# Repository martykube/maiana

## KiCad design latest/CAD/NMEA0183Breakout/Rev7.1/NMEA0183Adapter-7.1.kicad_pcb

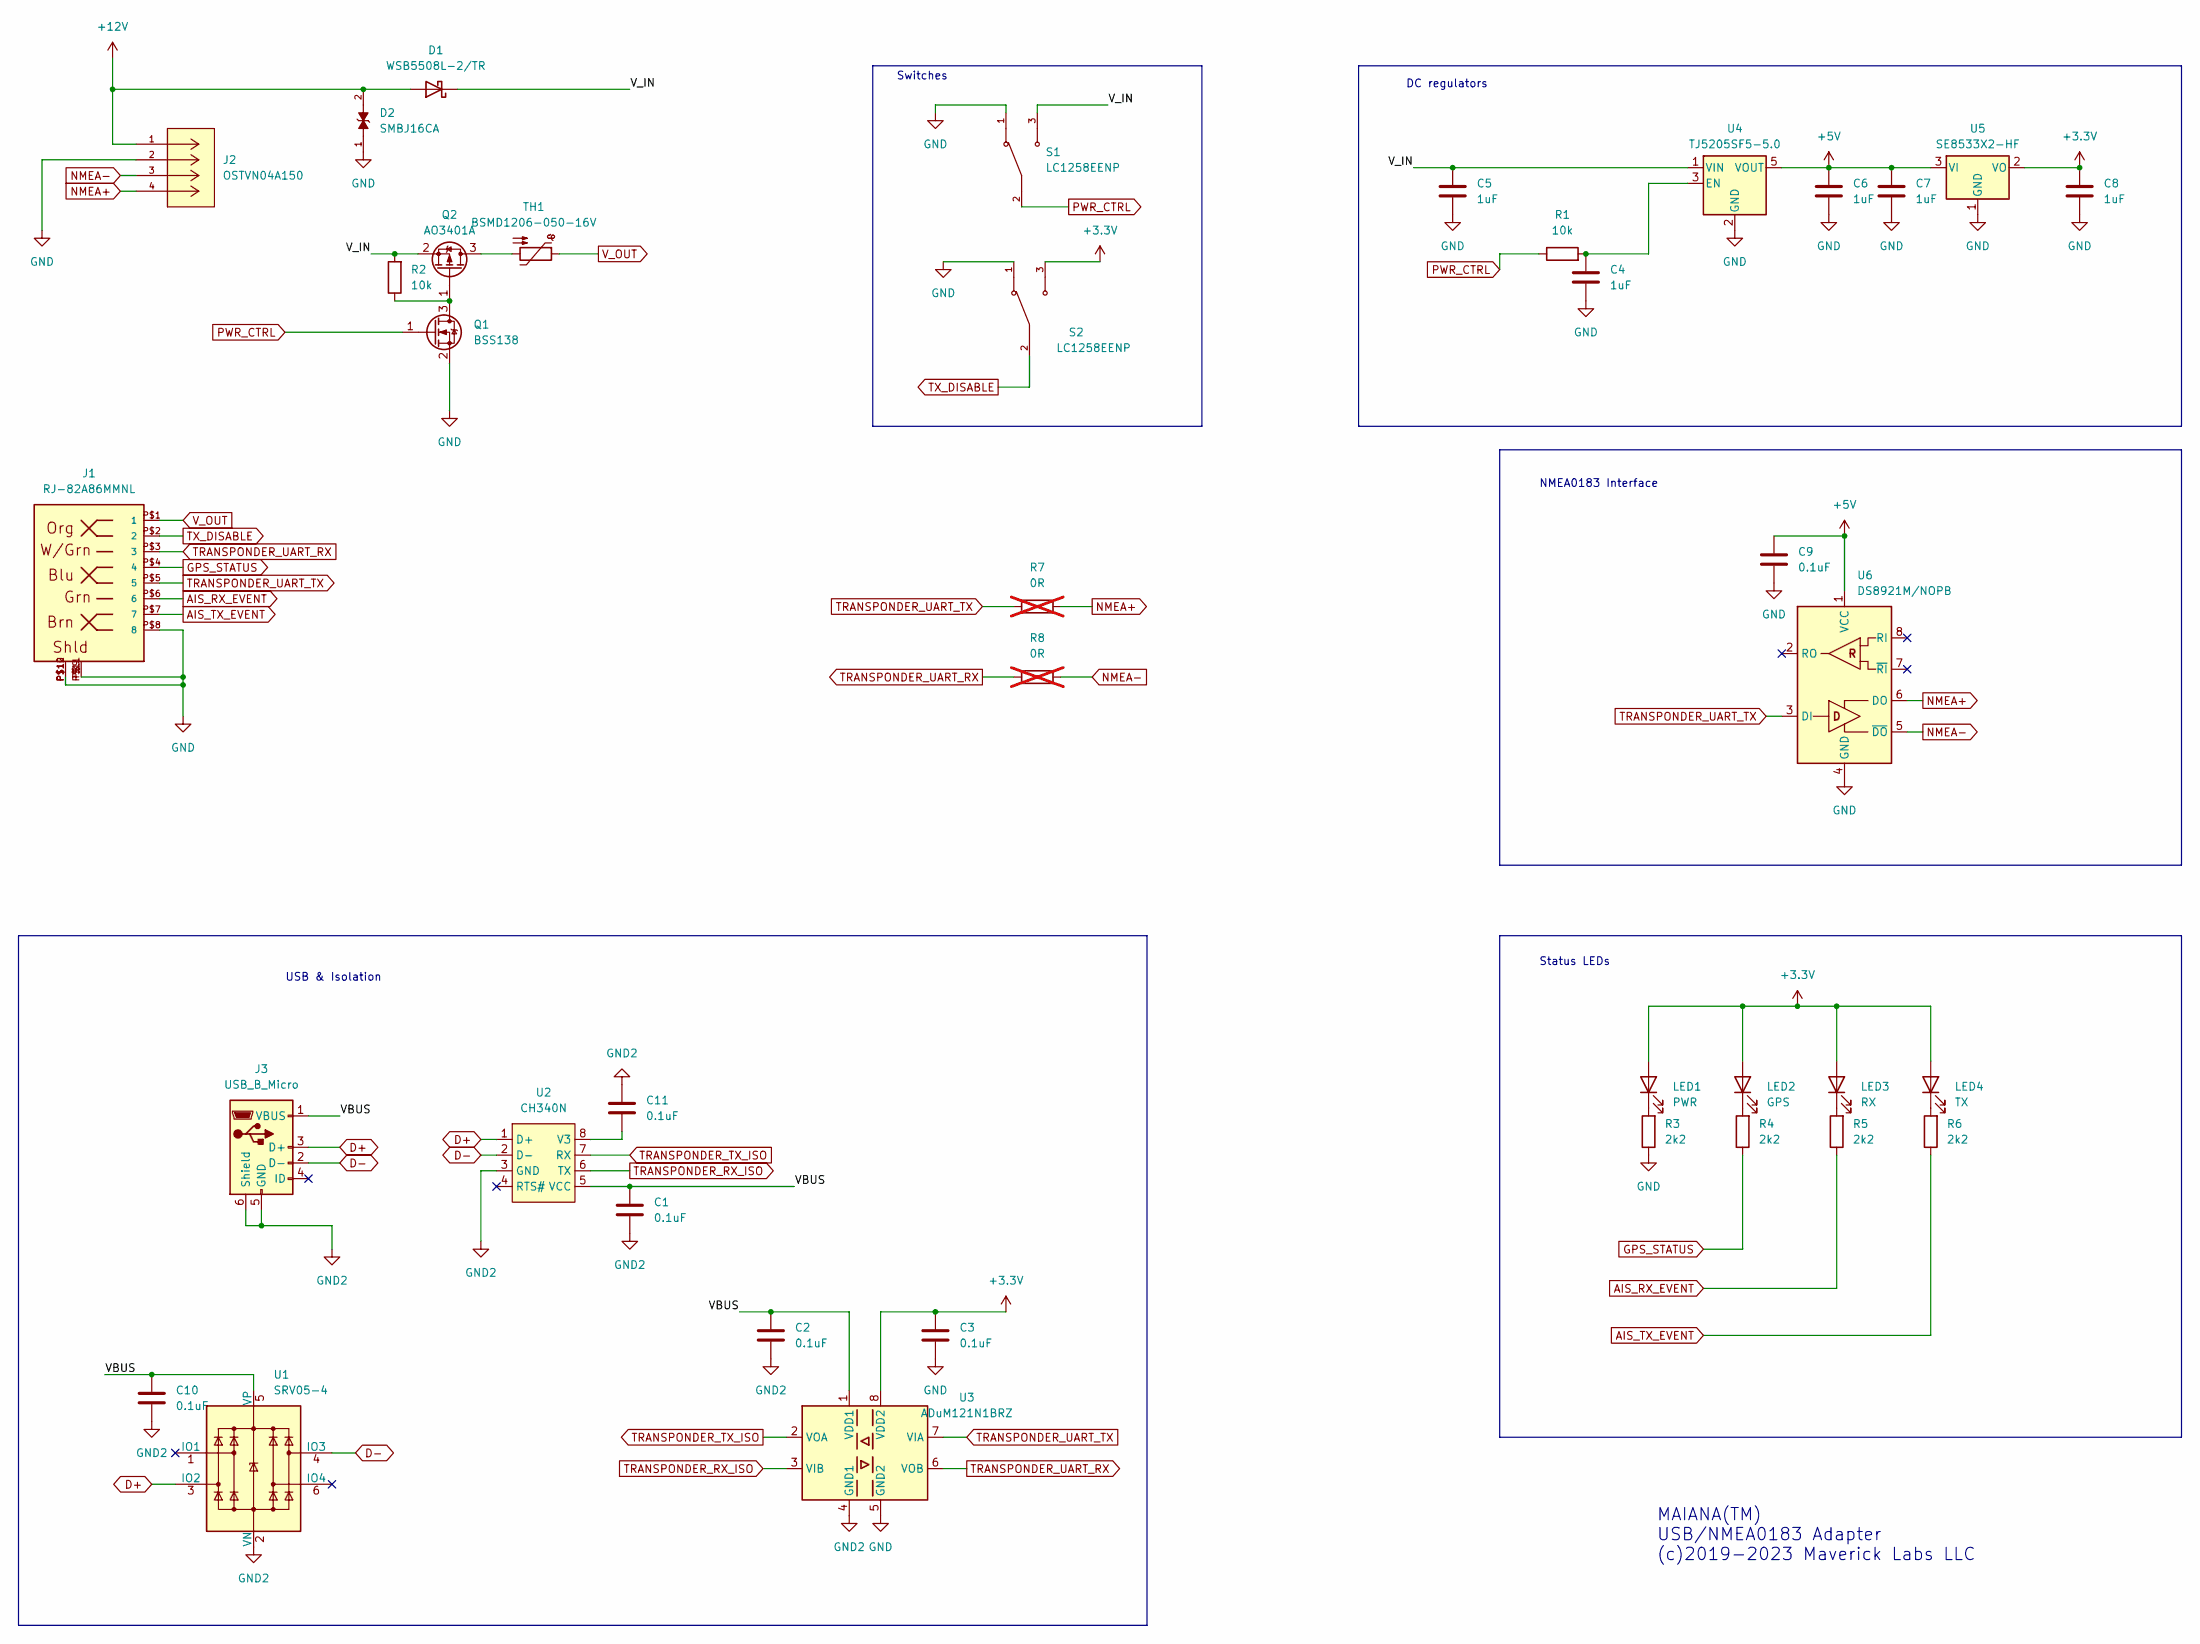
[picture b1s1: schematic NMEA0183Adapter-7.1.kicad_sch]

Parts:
C1, C2, C3, C9, C10, C11: 0.1uF; C_0603_1608Metric; LCSC C1591
C4, C5, C6, C7, C8: 1uF; C_0603_1608Metric; LCSC C15849
D1: WSB5508L-2/TR; D_SOD-123; LCSC C239542
D2: SMBJ16CA; DIOM4336X265N; PARTREV I2102; LCSC C113990
J1: RJ-82A86MMNL; PARTNO RJ-82A86MMNL; LCSC C7205195
J2: OSTVN04A150; CONN_OSTVN04A150_OST; MANUFACTURER_PART_NUMBER OSTVN04A150; DIGI-KEY_PART_NUMBER_1 ED10563-ND
J3: USB_B_Micro; USB_Micro-B_Amphenol_10118194_Horizontal; LCSC C132563
LED1: PWR; LED_1206_3216Metric; LCSC C14641
LED2: GPS; LED_1206_3216Metric; LCSC C14641
LED3: RX; LED_1206_3216Metric; LCSC C14641
LED4: TX; LED_1206_3216Metric; LCSC C14641
Q1: BSS138; SOT-23; LCSC C82045
Q2: AO3401A; SOT-23; LCSC C15127
R1, R2: 10k; R_0603_1608Metric; LCSC C25804
R3, R4, R5, R6: 2k2; R_0603_1608Metric; LCSC C4190
R7, R8: 0R; R_0603_1608Metric; not fitted
S1, S2: LC1258EENP; SW_LC1258EENP; PARTREV C
TH1: BSMD1206-050-16V; R_1206_3216Metric; LCSC C883124
U1: SRV05-4; SOT-23-6; LCSC C2836319
U2: CH340N; SO-8_3.9x4.9mm_P1.27mm; LCSC C2977777
U3: ADuM121N1BRZ; SOIC-8_3.9x4.9mm_P1.27mm; LCSC C190783
U4: TJ5205SF5-5.0; SOT-23-5; LCSC C126091
U5: SE8533X2-HF; SOT-23; LCSC C115016
U6: DS8921M/NOPB; SOIC-8_3.9x4.9mm_P1.27mm; LCSC C133584

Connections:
+3.3V: C3.1, C8.1, LED1.2 (A), LED2.2 (A), LED3.2 (A), LED4.2 (A), S2.3, U3.8 (VDD2), U5.2 (VO)
+5V: C6.1, C7.1, C9.1, U4.5 (VOUT), U5.3 (VI), U6.1 (VCC)
+12V: D1.2 (A), D2.2, J2.1
/VBUS: C1.1, C2.1, C10.1, J3.1 (VBUS), U1.5 (VP), U2.5 (VCC), U3.1 (VDD1)
/V_IN: C5.1, D1.1 (K), Q2.2 (S), R2.2, S1.3, U4.1 (VIN)
AIS_RX_EVENT: J1.P$6 (6), R5.1
AIS_TX_EVENT: J1.P$7 (7), R6.1
D+: J3.3 (D+), U1.3 (IO2), U2.1 (D+)
D-: J3.2 (D-), U1.4 (IO3), U2.2 (D-)
GND: C3.2, C4.2, C5.2, C6.2, C7.2, C8.2, C9.2, D2.1, J1.P$8 (8), J1.P$9, J1.P$10, J1.P$11, J1.P$12, J2.2, Q1.2 (S), R3.1, S1.1, S2.1, U3.5 (GND2), U4.2 (GND), U5.1 (GND), U6.4 (GND)
GND2: C1.2, C2.2, C10.2, C11.1, J3.5 (GND), J3.6 (Shield), U1.2 (VN), U2.3 (GND), U3.4 (GND1)
GPS_STATUS: J1.P$4 (4), R4.1
NMEA+: J2.4, R7.1, U6.6 (DO)
NMEA-: J2.3, R8.1, U6.5 (~DO)
unnamed: LED1.1 (K), R3.2
unnamed: LED2.1 (K), R4.2
unnamed: LED3.1 (K), R5.2
unnamed: LED4.1 (K), R6.2
unnamed: Q1.3 (D), Q2.1 (G), R2.1
unnamed: Q2.3 (D), TH1.2
unnamed: C11.2, U2.8 (V3)
unnamed: C4.1, R1.2, U4.3 (EN)
PWR_CTRL: Q1.1 (G), R1.1, S1.2
TRANSPONDER_RX_ISO: U2.6 (TX), U3.3 (VIB)
TRANSPONDER_TX_ISO: U2.7 (RX), U3.2 (VOA)
TRANSPONDER_UART_RX: J1.P$3 (3), R8.2, U3.6 (VOB)
TRANSPONDER_UART_TX: J1.P$5 (5), R7.2, U3.7 (VIA), U6.3 (DI)
TX_DISABLE: J1.P$2 (2), S2.2
V_OUT: J1.P$1 (1), TH1.1

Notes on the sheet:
USB & Isolation
Status LEDs
MAIANA(TM) USB/NMEA0183 Adapter (c)2019-2023 Maverick Labs LLC
NMEA0183 Interface
DC regulators
Switches

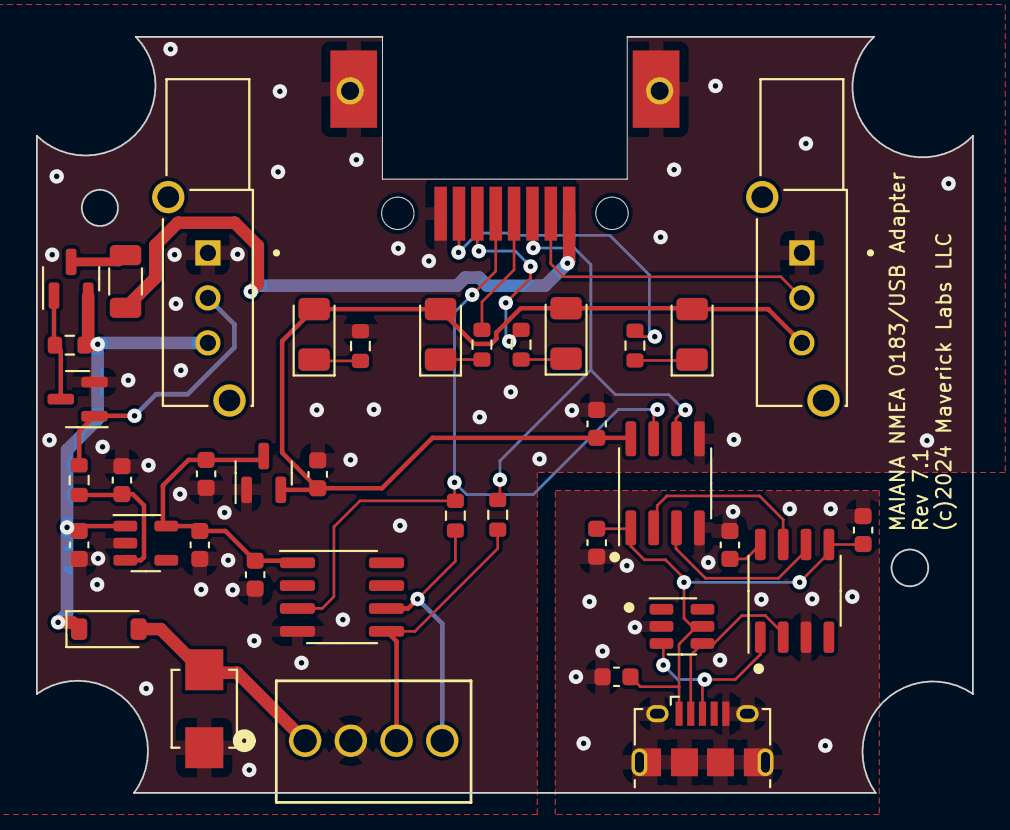
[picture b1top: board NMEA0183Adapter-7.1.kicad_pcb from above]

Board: 2 copper layers, 52.0 x 42.0 mm, 39 parts (0 on the bottom side), 29 nets.

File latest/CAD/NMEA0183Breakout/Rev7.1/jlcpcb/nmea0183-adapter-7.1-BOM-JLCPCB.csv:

Comment,Designator,Footprint,LCSC Part #
0.1uF 50V X7R,"C1,C2,C3,C9,C10,C11",0603,C1591
1uF 50V X5R,"C4,C5,C6,C7,C8",0603,C15849
WSB5508L-2/TR,D1,SOD-123,C239542
SMBJ16CA,D2,SMB,C113990
RJ45 FG RJ-055-1,J1,RJ-82A86MMNL,C7205195
10118194-0001LF,J3,USB_Micro-B,C132563
LED green,"LED1,LED2,LED3,LED4",1206,C14641
BSS138LT1G,Q1,SOT-23,C82045
AO3401A,Q2,SOT-23,C15127
10k,"R1,R2",0603,C25804
2.2k,"R3,R4,R5,R6",0603,C4190
BSMD1206-050-16V,TH1,1206,C883124
SRV05-4,U1,SOT-23-6,C2836319
CH340N,U2,SO-8,C2977777
ADUM121N1BRZ-RL7,U3,SOIC-8,C190783
TJ5205SF5-5.0,U4,SOT-23-5,C126091
SE8533X2-HF,U5,SOT-23,C115016
DS8921M/NOPB,U6,SOIC-8,C133584

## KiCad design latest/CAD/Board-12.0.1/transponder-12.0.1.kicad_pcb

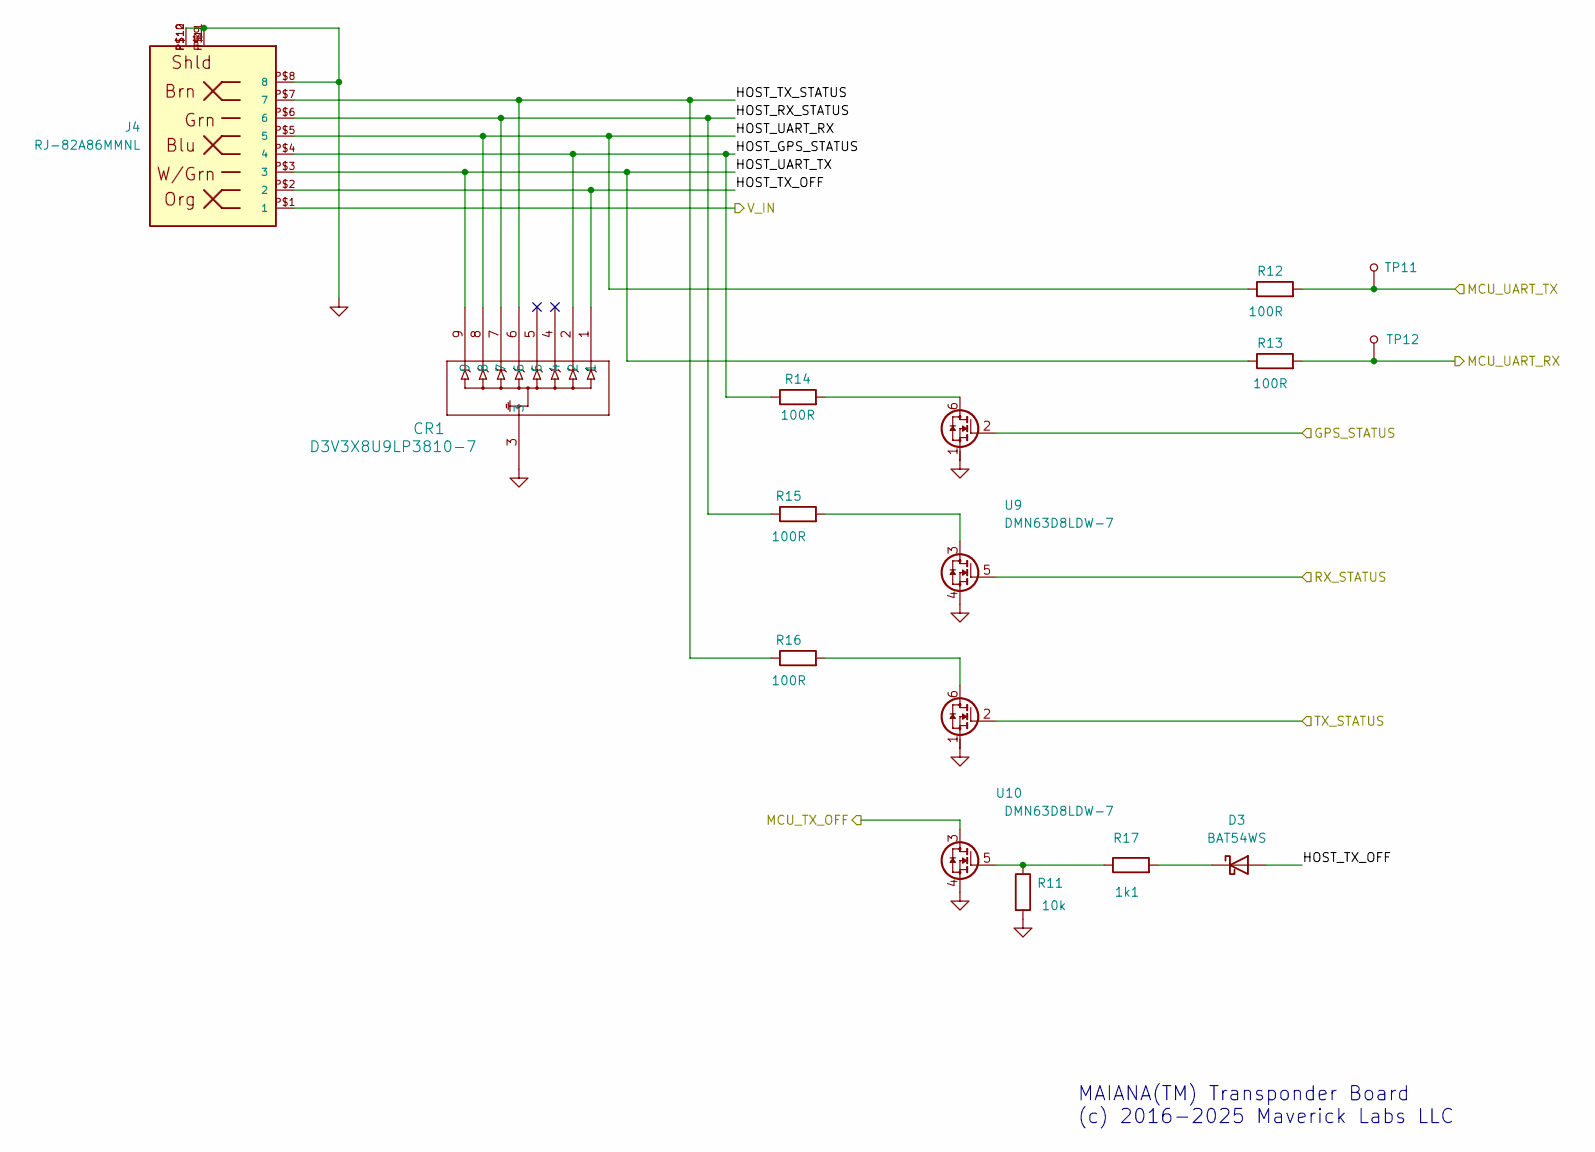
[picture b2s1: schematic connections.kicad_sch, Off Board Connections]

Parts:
CR1: D3V3X8U9LP3810-7; U-DFN3810-9TYPE_B_DIO; LCSC C1973794
D3: BAT54WS; D_SOD-323; LCSC C124205
J4: RJ-82A86MMNL; PARTNO RJ-82A86MMNL; LCSC C7205195
R11: 10k; R_0603_1608Metric; LCSC C25804
R12, R13, R14, R15, R16: 100R; R_0603_1608Metric; LCSC C22775
R17: 1k1; R_0603_1608Metric; LCSC C22764
TP11, TP12: TP_1.2MM
U9, U10: DMN63D8LDW-7; SOT-363_SC-70-6; LCSC C211422

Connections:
/Connections/GPS_STATUS: U9.2 (G1); also elsewhere on the board
/Connections/HOST_GPS_STATUS: CR1.2, J4.P$4 (4), R14.1
/Connections/HOST_RX_STATUS: CR1.7, J4.P$6 (6), R15.1
/Connections/HOST_TX_OFF: CR1.1, D3.2 (A), J4.P$2 (2)
/Connections/HOST_TX_STATUS: CR1.6, J4.P$7 (7), R16.1
/Connections/HOST_UART_RX: CR1.8, J4.P$5 (5), R12.1
/Connections/HOST_UART_TX: CR1.9, J4.P$3 (3), R13.1
/Connections/MCU_TX_OFF: U10.3 (D2); also elsewhere on the board
/Connections/MCU_UART_RX: R13.2, TP12.1; also elsewhere on the board
/Connections/MCU_UART_TX: R12.2, TP11.1; also elsewhere on the board
/Connections/RX_STATUS: U9.5 (G2); also elsewhere on the board
/Connections/TX_STATUS: U10.2 (G1); also elsewhere on the board
/Connections/V_IN: J4.P$1 (1); also elsewhere on the board
GND: CR1.3, J4.P$8 (8), J4.P$9, J4.P$10, J4.P$11, J4.P$12, R11.2, U9.1 (S1), U9.4 (S2), U10.1 (S1), U10.4 (S2); also elsewhere on the board
unnamed: D3.1 (K), R17.2
unnamed: R14.2, U9.6 (D1)
unnamed: R15.2, U9.3 (D2)
unnamed: R16.2, U10.6 (D1)
unnamed: R11.1, R17.1, U10.5 (G2)

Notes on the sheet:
MAIANA(TM) Transponder Board (c) 2016-2025 Maverick Labs LLC

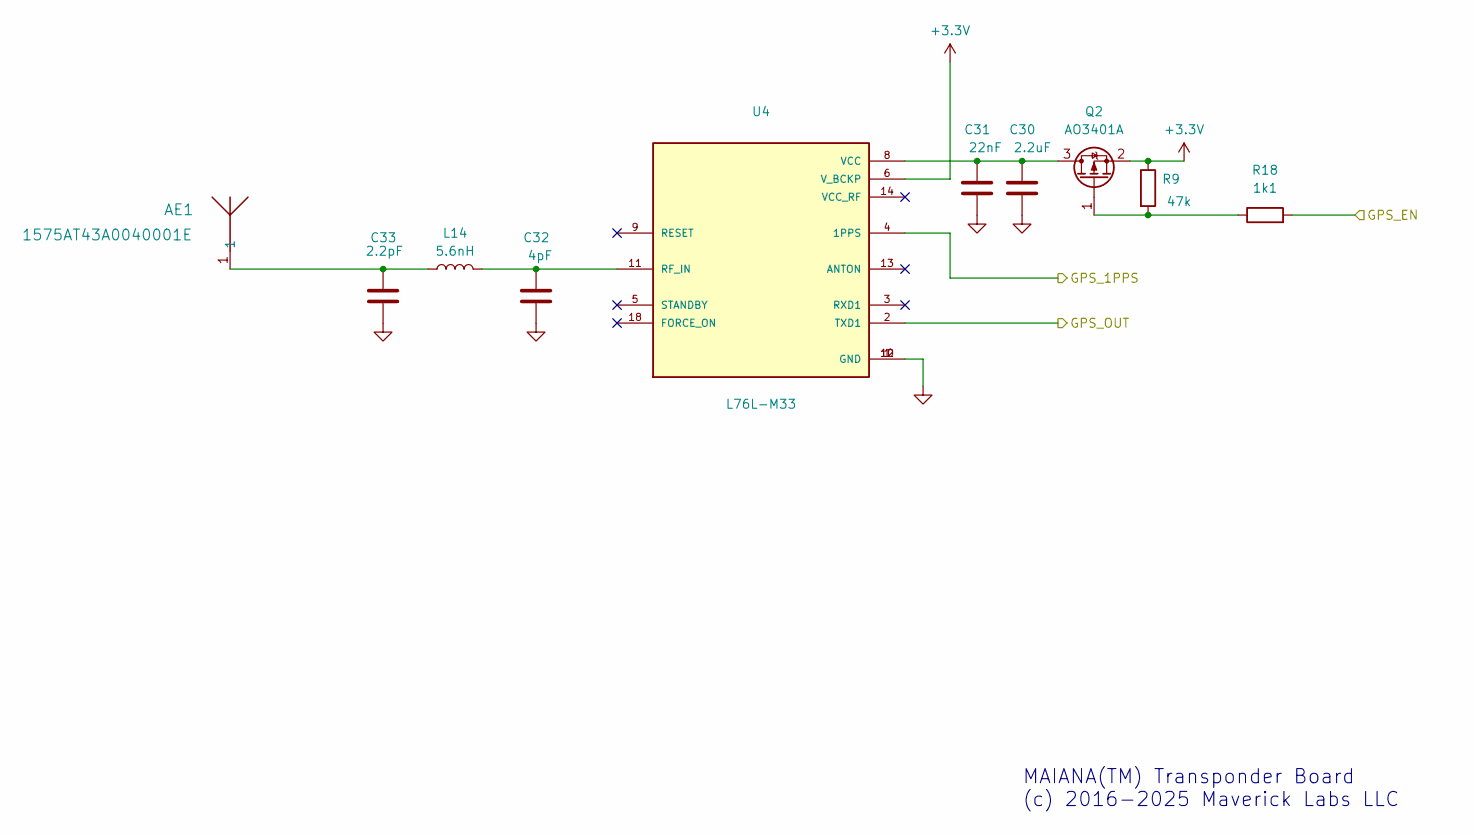
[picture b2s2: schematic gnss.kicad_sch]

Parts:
AE1: 1575AT43A0040001E; ANT_1575AT_JOT
C30: 2.2uF; C_0603_1608Metric; LCSC C380321
C31: 22nF; C_0603_1608Metric; LCSC C106222
C32: 4pF; C_0603_1608Metric; LCSC C437534
C33: 2.2pF; C_0603_1608Metric; LCSC C282246
L14: 5.6nH; L_0603_1608Metric; LCSC C98081
Q2: AO3401A; SOT-23; LCSC C15127
R9: 47k; R_0603_1608Metric; LCSC C25819
R18: 1k1; R_0603_1608Metric; LCSC C22764
U4: L76L-M33; XCVR_L76L-M33; LCSC C2916232

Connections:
+3.3V: Q2.2 (S), R9.1, U4.6 (V_BCKP); also elsewhere on the board
/GNSS/GPS_1PPS: U4.4 (1PPS); also elsewhere on the board
/GNSS/GPS_EN: R18.2; also elsewhere on the board
/GNSS/GPS_OUT: U4.2 (TXD1); also elsewhere on the board
GND: C30.1, C31.1, C32.1, C33.1, U4.1 (GND), U4.10 (GND), U4.12 (GND); also elsewhere on the board
unnamed: AE1.1, C33.2, L14.1
unnamed: C30.2, C31.2, Q2.3 (D), U4.8 (VCC)
unnamed: Q2.1 (G), R9.2, R18.1
unnamed: C32.2, L14.2, U4.11 (RF_IN)

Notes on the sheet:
MAIANA(TM) Transponder Board (c) 2016-2025 Maverick Labs LLC

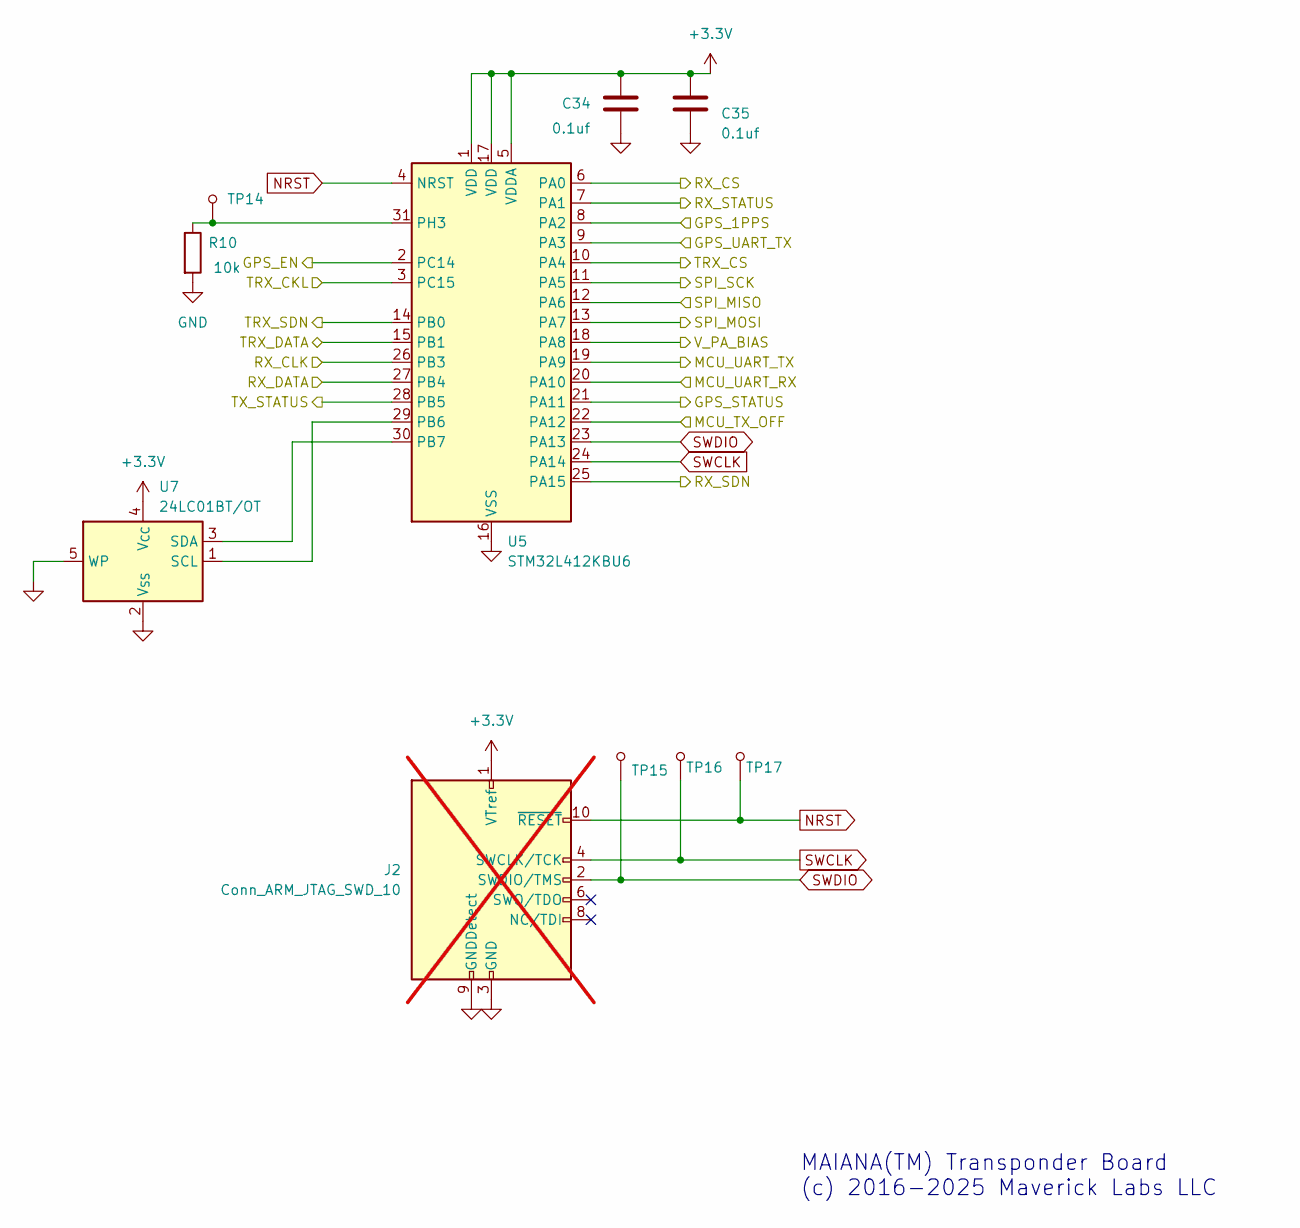
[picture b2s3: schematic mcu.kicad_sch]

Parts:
C34, C35: 0.1uf; C_0603_1608Metric; LCSC C14663
J2: Conn_ARM_JTAG_SWD_10; PinHeader_2x05_P1.27mm_Vertical_SMD; LCSC C5155080; not fitted
R10: 10k; R_0603_1608Metric; LCSC C25804
TP14, TP15, TP16, TP17: TP_1.2MM
U5: STM32L412KBU6; QFN-32-1EP_5x5mm_P0.5mm_EP3.45x3.45mm; LCSC C529439
U7: 24LC01BT/OT; SOT-23-5; LCSC C511269

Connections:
+3.3V: C34.2, C35.2, J2.1 (VTref), U5.1 (VDD), U5.5 (VDDA), U5.17 (VDD), U7.4 (V_{CC}); also elsewhere on the board
/Connections/GPS_STATUS: U5.21 (PA11); also elsewhere on the board
/Connections/MCU_TX_OFF: U5.22 (PA12); also elsewhere on the board
/Connections/MCU_UART_RX: U5.20 (PA10); also elsewhere on the board
/Connections/MCU_UART_TX: U5.19 (PA9); also elsewhere on the board
/Connections/RX_STATUS: U5.7 (PA1); also elsewhere on the board
/Connections/TX_STATUS: U5.28 (PB5); also elsewhere on the board
/GNSS/GPS_1PPS: U5.8 (PA2); also elsewhere on the board
/GNSS/GPS_EN: U5.2 (PC14); also elsewhere on the board
/GNSS/GPS_OUT: U5.9 (PA3); also elsewhere on the board
/MCU/RX_CLK: U5.26 (PB3); also elsewhere on the board
/MCU/RX_CS: U5.6 (PA0); also elsewhere on the board
/MCU/RX_DATA: U5.27 (PB4); also elsewhere on the board
/MCU/RX_SDN: U5.25 (PA15); also elsewhere on the board
/MCU/SPI_MISO: U5.12 (PA6); also elsewhere on the board
/MCU/SPI_MOSI: U5.13 (PA7); also elsewhere on the board
/MCU/SPI_SCK: U5.11 (PA5); also elsewhere on the board
/MCU/TRX_CKL: U5.3 (PC15); also elsewhere on the board
/MCU/TRX_CS: U5.10 (PA4); also elsewhere on the board
/MCU/TRX_DATA: U5.15 (PB1); also elsewhere on the board
/MCU/TRX_SDN: U5.14 (PB0); also elsewhere on the board
/MCU/V_PA_BIAS: U5.18 (PA8); also elsewhere on the board
GND: C34.1, C35.1, J2.3 (GND), J2.5 (GND), J2.9 (GNDDetect), R10.2, U5.16 (VSS), U5.32 (VSS), U5.33 (VSS), U7.2 (V_{SS}), U7.5 (WP); also elsewhere on the board
NRST: J2.10 (~RESET), TP17.1, U5.4 (NRST)
unnamed: R10.1, TP14.1, U5.31 (PH3)
unnamed: U5.29 (PB6), U7.1 (SCL)
unnamed: U5.30 (PB7), U7.3 (SDA)
SWCLK: J2.4 (SWCLK/TCK), TP16.1, U5.24 (PA14)
SWDIO: J2.2 (SWDIO/TMS), TP15.1, U5.23 (PA13)

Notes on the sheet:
MAIANA(TM) Transponder Board (c) 2016-2025 Maverick Labs LLC

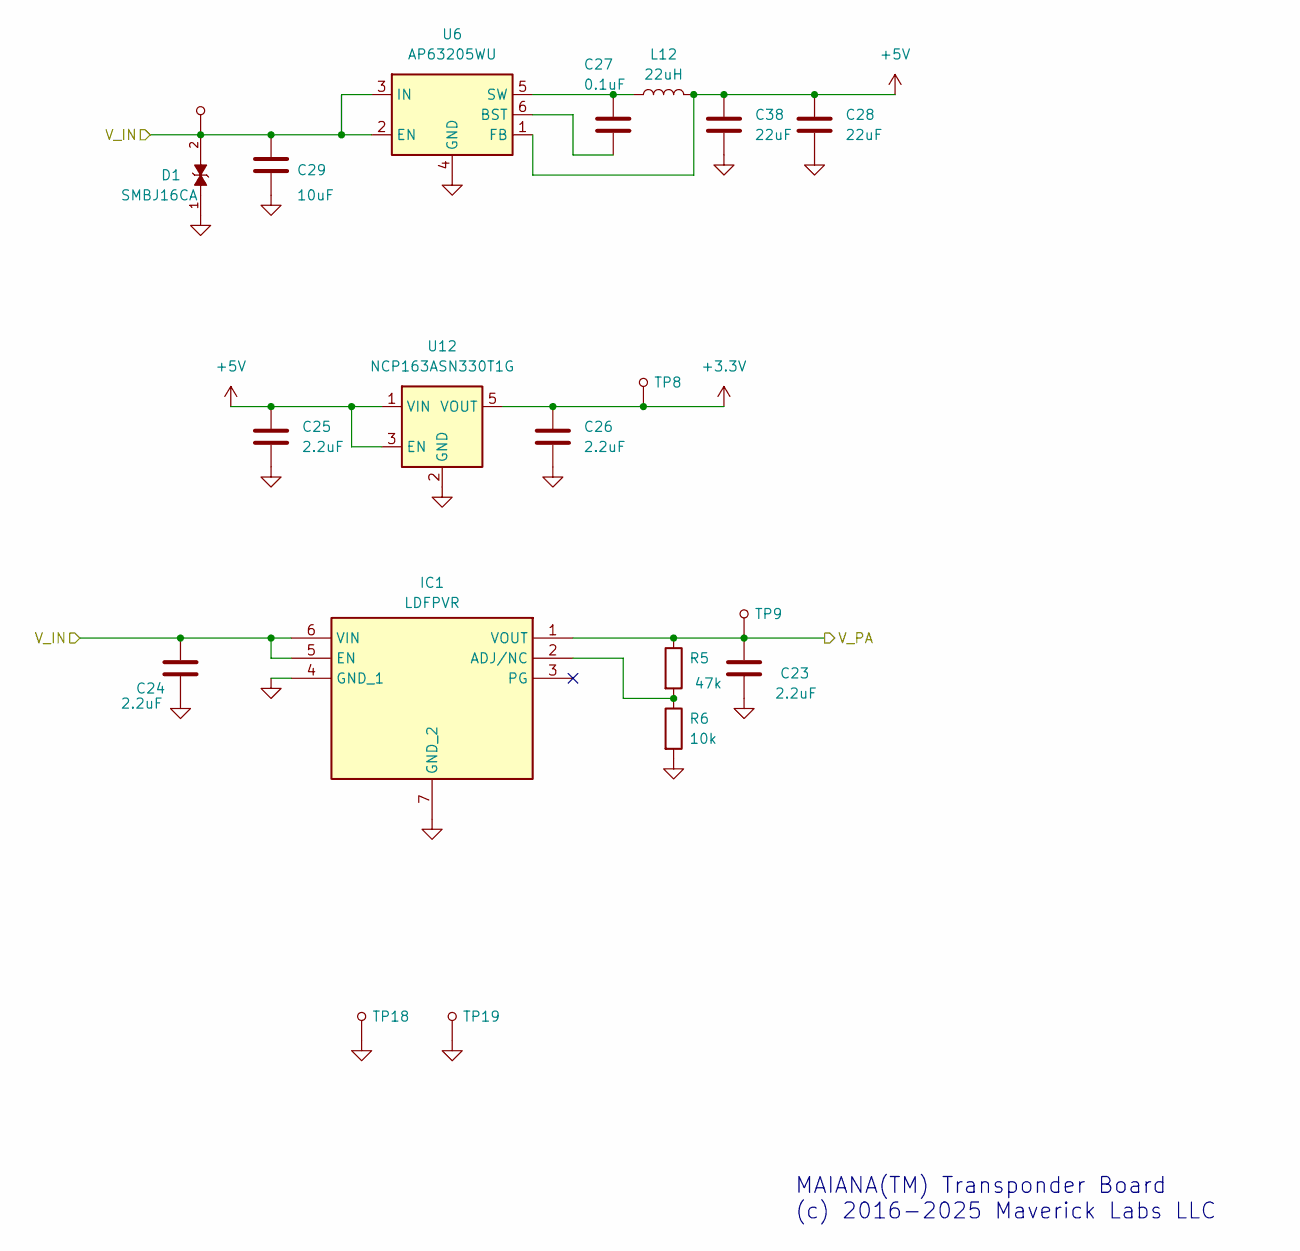
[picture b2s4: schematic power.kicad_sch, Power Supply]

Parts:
C23, C24, C25, C26: 2.2uF; C_0603_1608Metric; LCSC C380321
C27: 0.1uF; C_0603_1608Metric; LCSC C14663
C28, C38: 22uF; C_0805_2012Metric; LCSC C20416420
C29: 10uF; C_0805_2012Metric; LCSC C18185759
D1: SMBJ16CA; DIOM4336X265N; PARTREV I2102; LCSC C113990
IC1: LDFPVR; SON65P200X200X100-7N-D; Mouser Part Number 511-LDFPVR; LCSC C2969978
L12: 22uH; L_1210_3225Metric; LCSC C307600
R5: 47k; R_0603_1608Metric; LCSC C25819
R6: 10k; R_0603_1608Metric; LCSC C25804
TP8, TP9, TP10, TP18, TP19: TP_1.2MM
U6: AP63205WU; TSOT-23-6; LCSC C2071056
U12: NCP163ASN330T1G; SOT-23-5; LCSC C603656

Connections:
+3.3V: C26.1, TP8.1, U12.5 (VOUT); also elsewhere on the board
+5V: C25.1, C28.1, C38.1, L12.2, U6.1 (FB), U12.1 (VIN), U12.3 (EN)
/Connections/V_IN: C24.2, C29.1, D1.2, IC1.5 (EN), IC1.6 (VIN), TP10.1, U6.2 (EN), U6.3 (IN); also elsewhere on the board
/Power/V_PA: C23.2, IC1.1 (VOUT), R5.1, TP9.1; also elsewhere on the board
GND: C23.1, C24.1, C25.2, C26.2, C28.2, C29.2, C38.2, D1.1, IC1.4 (GND_1), IC1.7 (GND_2), R6.2, TP18.1, TP19.1, U6.4 (GND), U12.2 (GND); also elsewhere on the board
unnamed: IC1.2 (ADJ/NC), R5.2, R6.1
unnamed: C27.1, U6.6 (BST)
unnamed: C27.2, L12.1, U6.5 (SW)

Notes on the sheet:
MAIANA(TM) Transponder Board (c) 2016-2025 Maverick Labs LLC

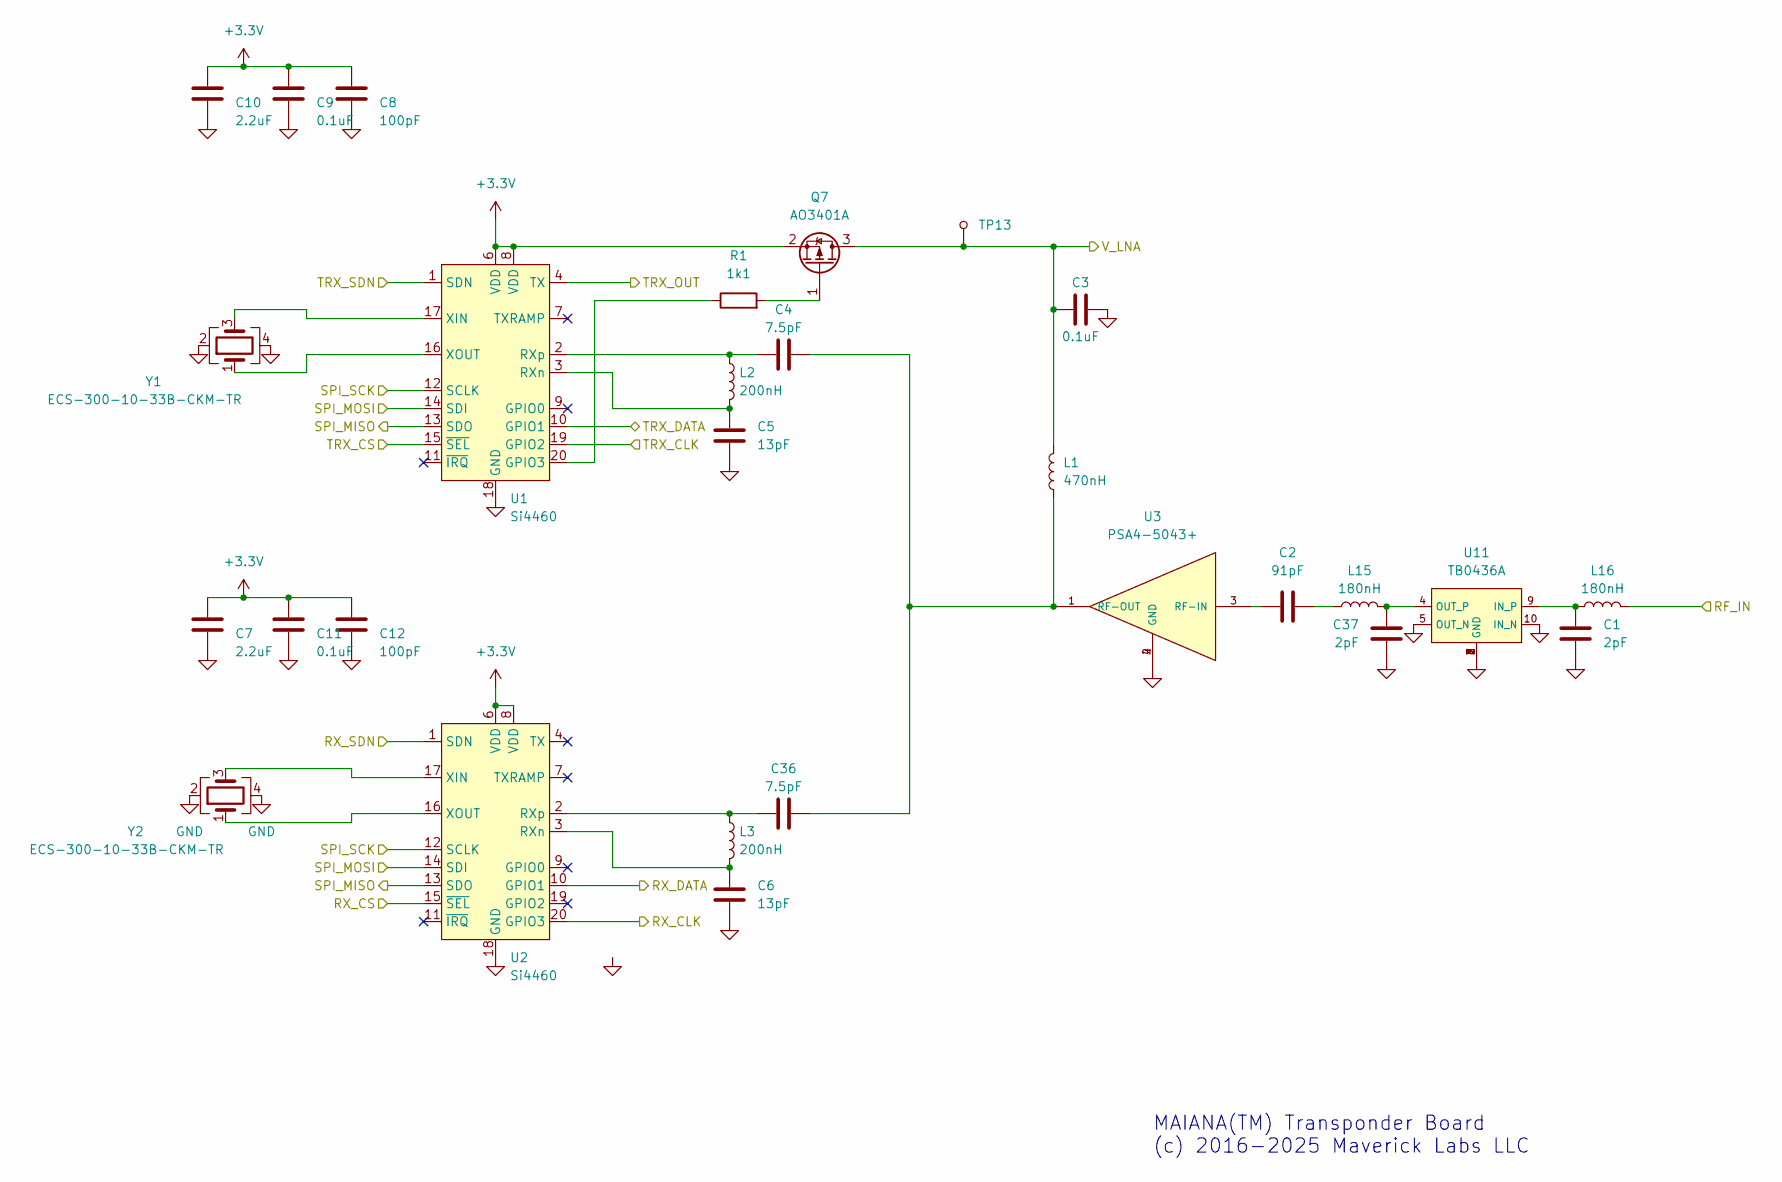
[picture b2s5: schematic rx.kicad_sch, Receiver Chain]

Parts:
C1, C37: 2pF; C_0603_1608Metric; LCSC C81437
C2: 91pF; C_0603_1608Metric; LCSC C701317
C3, C9, C11: 0.1uF; C_0603_1608Metric; LCSC C14663
C4, C36: 7.5pF; C_0402_1005Metric; LCSC C88938
C5, C6: 13pF; C_0402_1005Metric; LCSC C130119
C7, C10: 2.2uF; C_0603_1608Metric; LCSC C380321
C8, C12: 100pF; C_0603_1608Metric; LCSC C71664
L1: 470nH; L_0603_1608Metric; LCSC C113132
L2, L3: 200nH; L_0402_1005Metric; LCSC C2045944
L15, L16: 180nH; L_0603_1608Metric; LCSC C98091
Q7: AO3401A; SOT-23; LCSC C15127
R1: 1k1; R_0603_1608Metric; LCSC C22764
TP13: TP_1.2MM
U1, U2: Si4460; QFN-20-1EP_4x4mm_P0.5mm_EP2.6x2.6mm_ThermalVias; LCSC C2151590
U3: PSA4-5043+; PSA4-5043_; LCSC C5240848
U11: TB0436A
Y1, Y2: ECS-300-10-33B-CKM-TR; Crystal_SMD_3225-4Pin_3.2x2.5mm

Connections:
+3.3V: C7.2, C8.2, C9.2, C10.2, C11.2, C12.2, Q7.2 (S), U1.6 (VDD), U1.8 (VDD), U2.6 (VDD), U2.8 (VDD); also elsewhere on the board
/MCU/RX_CLK: U2.20 (GPIO3); also elsewhere on the board
/MCU/RX_CS: U2.15 (~SEL); also elsewhere on the board
/MCU/RX_DATA: U2.10 (GPIO1); also elsewhere on the board
/MCU/RX_SDN: U2.1 (SDN); also elsewhere on the board
/MCU/SPI_MISO: U1.13 (SDO), U2.13 (SDO); also elsewhere on the board
/MCU/SPI_MOSI: U1.14 (SDI), U2.14 (SDI); also elsewhere on the board
/MCU/SPI_SCK: U1.12 (SCLK), U2.12 (SCLK); also elsewhere on the board
/MCU/TRX_CKL: U1.19 (GPIO2); also elsewhere on the board
/MCU/TRX_CS: U1.15 (~SEL); also elsewhere on the board
/MCU/TRX_DATA: U1.10 (GPIO1); also elsewhere on the board
/MCU/TRX_SDN: U1.1 (SDN); also elsewhere on the board
/Receiver/RF_IN: L16.2; also elsewhere on the board
/Receiver/TRX_OUT: U1.4 (TX); also elsewhere on the board
/Receiver/V_LNA: C3.1, L1.2, Q7.3 (D), TP13.1; also elsewhere on the board
GND: C1.2, C3.2, C5.2, C6.2, C7.1, C8.1, C9.1, C10.1, C11.1, C12.1, C37.2, U1.18 (GND), U1.21 (GND), U2.18 (GND), U2.21 (GND), U3.2 (GND), U3.4 (GND), U11.1, U11.2 (GND), U11.3, U11.5 (OUT_N), U11.6, U11.7, U11.8, U11.10 (IN_N), Y1.2, Y1.4, Y2.2, Y2.4; also elsewhere on the board
unnamed: C2.2, L15.1
unnamed: Q7.1 (G), R1.2
unnamed: R1.1, U1.20 (GPIO3)
unnamed: C5.1, L2.2, U1.3 (RXn)
unnamed: C4.1, L2.1, U1.2 (RXp)
unnamed: U1.17 (XIN), Y1.3
unnamed: U1.16 (XOUT), Y1.1
unnamed: C6.1, L3.2, U2.3 (RXn)
unnamed: C36.1, L3.1, U2.2 (RXp)
unnamed: U2.17 (XIN), Y2.3
unnamed: U2.16 (XOUT), Y2.1
unnamed: C2.1, U3.3 (RF-IN)
unnamed: C4.2, C36.2, L1.1, U3.1 (RF-OUT)
unnamed: C1.1, L16.1, U11.9 (IN_P)
unnamed: C37.1, L15.2, U11.4 (OUT_P)

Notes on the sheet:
MAIANA(TM) Transponder Board (c) 2016-2025 Maverick Labs LLC

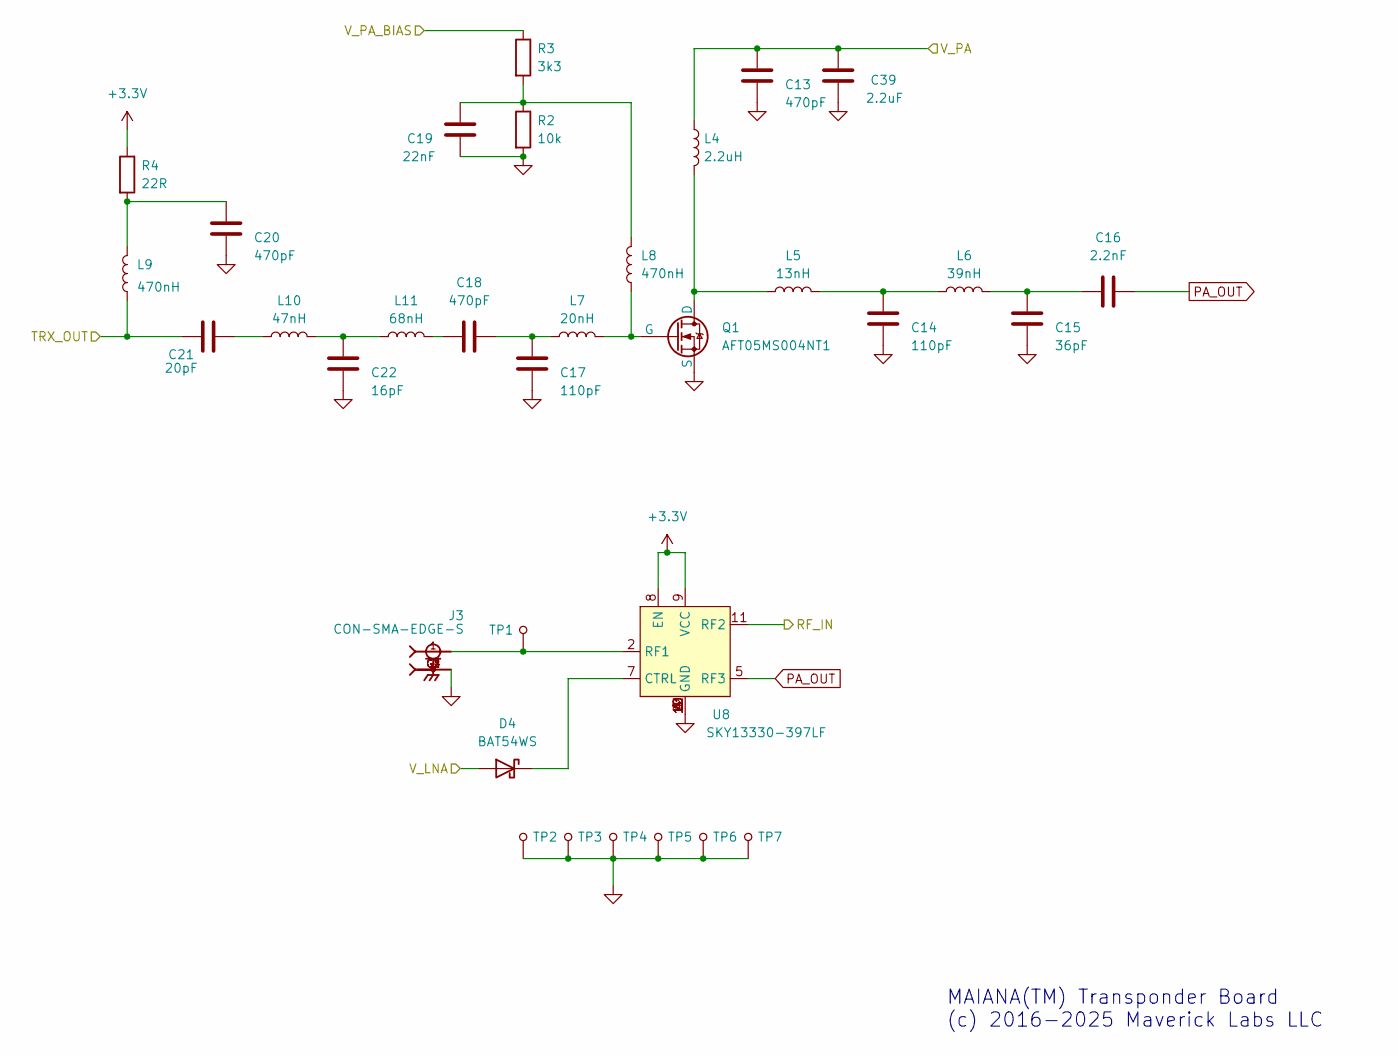
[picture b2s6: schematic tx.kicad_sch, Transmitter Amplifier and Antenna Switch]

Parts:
C13, C18, C20: 470pF; C_0603_1608Metric; LCSC C85979
C14, C17: 110pF; C_0603_1608Metric; LCSC C327208
C15: 36pF; C_0603_1608Metric; LCSC C134070
C16: 2.2nF; C_0603_1608Metric; LCSC C77033
C19: 22nF; C_0603_1608Metric; LCSC C106222
C21: 20pF; C_0603_1608Metric; LCSC C77030
C22: 16pF; C_0603_1608Metric; LCSC C327125
C39: 2.2uF; C_0603_1608Metric; LCSC C380321
D4: BAT54WS; D_SOD-323; LCSC C124205
J3: CON-SMA-EDGE-S; RFSOLUTIONS_CON-SMA-EDGE-S; PARTREV 1; DigiKey_Part_Number CON-SMA-EDGE-S-ND
L4: 2.2uH; L_0603_1608Metric; LCSC C55265173
L5: 13nH; L_0603_1608Metric; LCSC C701184
L6: 39nH; L_0603_1608Metric; LCSC C86134
L7: 20nH; L_0603_1608Metric; LCSC C77124
L8, L9: 470nH; L_0603_1608Metric; LCSC C113132
L10: 47nH; L_0603_1608Metric; LCSC C98076
L11: 68nH; L_0603_1608Metric; LCSC C86135
Q1: AFT05MS004NT1; SOT-89-3; LCSC C713822
R2: 10k; R_0603_1608Metric; LCSC C25804
R3: 3k3; R_0603_1608Metric; LCSC C22978
R4: 22R; R_0603_1608Metric; LCSC C23345
TP1: TP_1.0MM
TP2, TP3, TP4, TP5, TP6, TP7: TP_1.2MM
U8: SKY13330-397LF; QFN50P200X200X65-13N; LCSC C2654715

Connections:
+3.3V: R4.1, U8.8 (EN), U8.9 (VCC); also elsewhere on the board
/MCU/V_PA_BIAS: R3.1; also elsewhere on the board
/Power/V_PA: C13.2, C39.2, L4.1; also elsewhere on the board
/Receiver/RF_IN: U8.11 (RF2); also elsewhere on the board
/Receiver/TRX_OUT: C21.1, L9.1; also elsewhere on the board
/Receiver/V_LNA: D4.2 (A); also elsewhere on the board
GND: C13.1, C14.1, C15.1, C17.1, C19.1, C20.1, C22.1, C39.1, J3.G1, J3.G2, J3.G3, J3.G4, Q1.2 (S), R2.2, TP2.1, TP3.1, TP4.1, TP5.1, TP6.1, TP7.1, U8.1 (GND), U8.3 (GND), U8.4 (GND), U8.6 (GND), U8.10 (GND), U8.12 (GND), U8.13 (GND); also elsewhere on the board
unnamed: C14.2, L5.2, L6.1
unnamed: C15.2, C16.1, L6.2
unnamed: C17.2, C18.2, L7.1
unnamed: C18.1, L11.2
unnamed: C19.2, L8.2, R2.1, R3.2
unnamed: C20.2, L9.2, R4.2
unnamed: C21.2, L10.1
unnamed: C22.2, L10.2, L11.1
unnamed: D4.1 (K), U8.7 (CTRL)
unnamed: L4.2, L5.1, Q1.3 (D)
unnamed: L7.2, L8.1, Q1.1 (G)
unnamed: J3.1, TP1.1, U8.2 (RF1)
PA_OUT: C16.2, U8.5 (RF3)

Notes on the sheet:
MAIANA(TM) Transponder Board (c) 2016-2025 Maverick Labs LLC

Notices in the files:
latest/CAD/NMEA0183Breakout/Rev7.1/NMEA0183Adapter-7.1.kicad_pcb:
(c)2024 Maverick Labs LLC
latest/CAD/NMEA2000Breakout/Rev8.1/NMEA2000Adapter-8.1.kicad_pcb:
(c)2023 Maverick Labs LLC
parts and their libraries:
COPYRIGHT: Copyright (C) 2021 Ultra Librarian. All rights reserved.
